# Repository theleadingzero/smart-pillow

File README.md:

# smart-pillow
Resources to construct an e-textile, touch-sensitive pillow to control streaming audio/video with Arduino and Trill Craft.

See the [wiki](https://github.com/theleadingzero/smart-pillow/wiki) for full documentation.

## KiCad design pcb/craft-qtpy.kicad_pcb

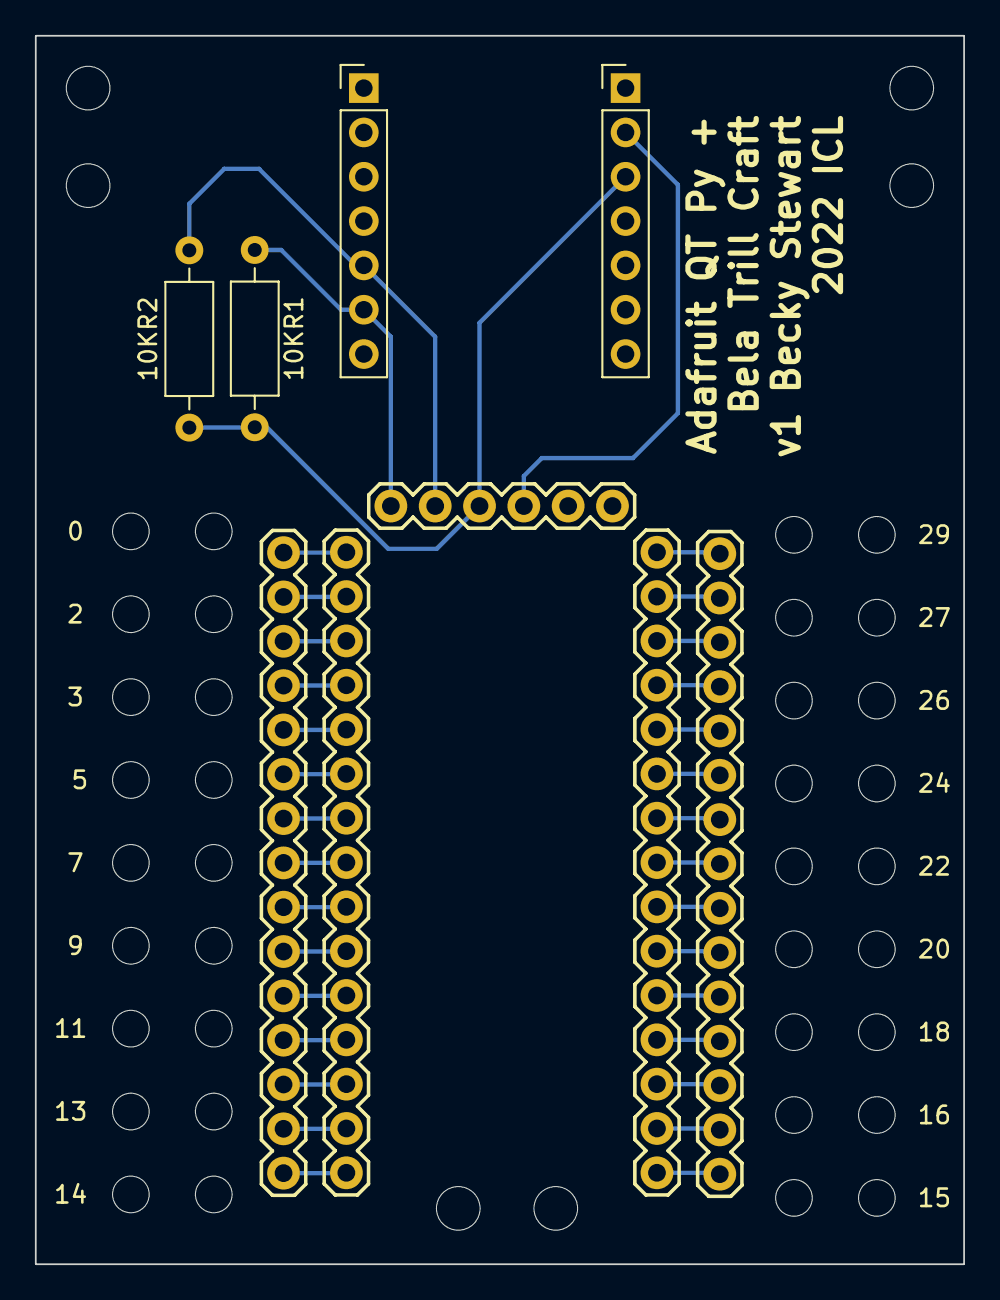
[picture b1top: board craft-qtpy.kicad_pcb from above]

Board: 2 copper layers, 53.2 x 70.4 mm, 27 parts (0 on the bottom side), 34 nets.

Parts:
0, 2, 3, 5, 7, 9, 11, 13, 14, 15, 16, 18, 20, 22, 24, 26, 27, 29: MountingHole_2.1mm
10KR1, 10KR2: R; R_Axial_DIN0207_L6.3mm_D2.5mm_P10.16mm_Horizontal
Craft-0-14, Craft-15-29: Conn_01x15_Female; 1X15
Craft-I2C1: Conn_01x06_Female; 1X06
QTPy-Left1: Conn_01x07_Female; PinHeader_1x07_P2.54mm_Vertical
QTPy-Right1: Conn_01x07_Female; PinHeader_1x07_P2.54mm_Vertical
Wires-Out-Left1: Conn_01x15_Male; 1X15
Wires-Out-Right1: Conn_01x15_Male; 1X15

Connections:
unnamed: Craft-15-29.1, Wires-Out-Right1.1
unnamed: Craft-15-29.2, Wires-Out-Right1.2
unnamed: Craft-15-29.3, Wires-Out-Right1.3
unnamed: Craft-15-29.4, Wires-Out-Right1.4
unnamed: Craft-15-29.5, Wires-Out-Right1.5
unnamed: Craft-15-29.6, Wires-Out-Right1.6
unnamed: Craft-15-29.7, Wires-Out-Right1.7
unnamed: Craft-15-29.8, Wires-Out-Right1.8
unnamed: Craft-15-29.9, Wires-Out-Right1.9
unnamed: Craft-15-29.10, Wires-Out-Right1.10
unnamed: Craft-15-29.11, Wires-Out-Right1.11
unnamed: Craft-15-29.12, Wires-Out-Right1.12
unnamed: Craft-15-29.13, Wires-Out-Right1.13
unnamed: Craft-15-29.14, Wires-Out-Right1.14
unnamed: Craft-15-29.15, Wires-Out-Right1.15
unnamed: 10KR2.2, Craft-I2C1.5, QTPy-Left1.5
unnamed: 10KR1.2, Craft-I2C1.6, QTPy-Left1.6
unnamed: Craft-I2C1.3, QTPy-Right1.2
unnamed: 10KR1.1, 10KR2.1, Craft-I2C1.4, QTPy-Right1.3
unnamed: Craft-0-14.1, Wires-Out-Left1.1
unnamed: Craft-0-14.2, Wires-Out-Left1.2
unnamed: Craft-0-14.3, Wires-Out-Left1.3
unnamed: Craft-0-14.4, Wires-Out-Left1.4
unnamed: Craft-0-14.5, Wires-Out-Left1.5
unnamed: Craft-0-14.6, Wires-Out-Left1.6
unnamed: Craft-0-14.7, Wires-Out-Left1.7
unnamed: Craft-0-14.8, Wires-Out-Left1.8
unnamed: Craft-0-14.9, Wires-Out-Left1.9
unnamed: Craft-0-14.10, Wires-Out-Left1.10
unnamed: Craft-0-14.11, Wires-Out-Left1.11
unnamed: Craft-0-14.12, Wires-Out-Left1.12
unnamed: Craft-0-14.13, Wires-Out-Left1.13
unnamed: Craft-0-14.14, Wires-Out-Left1.14
unnamed: Craft-0-14.15, Wires-Out-Left1.15

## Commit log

2022-05-19 Linked to wiki
2022-05-23 Simple example that prints raw values saved in global array
2022-05-23 Brain dump of functionality, but basics all working
2022-05-25 Added design worksheet
2022-05-25 Added basic example
2022-05-30 First set of functionality working, all done in single sketch.
2022-05-30 Added menu screenshot
2022-05-30 Added download screenshot
2022-05-30 Another screenshot
2022-06-01 Two example sketches
2022-06-01 Added screenshot
2022-06-01 Adding design worksheet
2022-06-01 Minor changes in layout
2022-06-03 Adding copper tape images
2022-06-03 Adjusted copper tape images
2022-06-03 Adding final build photos
2022-06-04 Research participant documents
2022-06-04 Adding snap wire making images
2022-06-04 PCB gerbers and KiCAD files
2022-06-07 Added animated gif
2022-10-20 Demoing how to commit and push
